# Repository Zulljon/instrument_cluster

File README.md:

View this project on [CADLAB.io](https://cadlab.io/project/2495). 

# ECU emulator v3.1a
PCB part of project (source codes unavailable!)

## Scheme

## PCB

### With FreeCAD PCB mod

### With FreeCAD KiCAD StepUp mod

## Tools
- KiCAD v4.0.7
- FreeCAD v0.15

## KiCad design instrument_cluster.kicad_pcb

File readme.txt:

Name of each file consists from name of project and it`s purpose, for example:
	Rover_Commander_v3.1a-B.Cu.gbr
		Rover_Commander_v3.1a - project name
		-B.Cu.gbr - нижний слой меди

соответственно:
	
	*-B.Cu.gbr  	-	back copper layer
	*-B.Fab.gbr 	-	footprint assemly on board`s back 
	*-B.Mask.gbr	-	solder mask on board`s back
	*-B.Paste.gbr	-	solder paste on board`s back
	*-B.SilkS.gbr	-	silkscreen on board`s back
	*-B.CrtYd.gbr	-	footprints courtyards on board`s back
	*-B.Adhes.gbr	-	adhesive on board`s back

	*-F.Cu.gbr  	-	front copper layer
	*-F.Fab.gbr 	-	footprint assemly on board`s front
	*-F.Mask.gbr	-	solder mask on board`s front
	*-F.Paste.gbr	-	solder paste on board`s front
	*-F.SilkS.gbr	-	silkscreen on board`s front
	*-F.CrtYd.gbr	-	footprints courtyards on board`s front
	*-F.Adhes.gbr	-	adhesive on board`s front

	*-Edge.Cuts.gbr	-	board`s perimeter definition
	*.drl			-	excellon drill file
	*-drl_map.gbr	-	map drill file

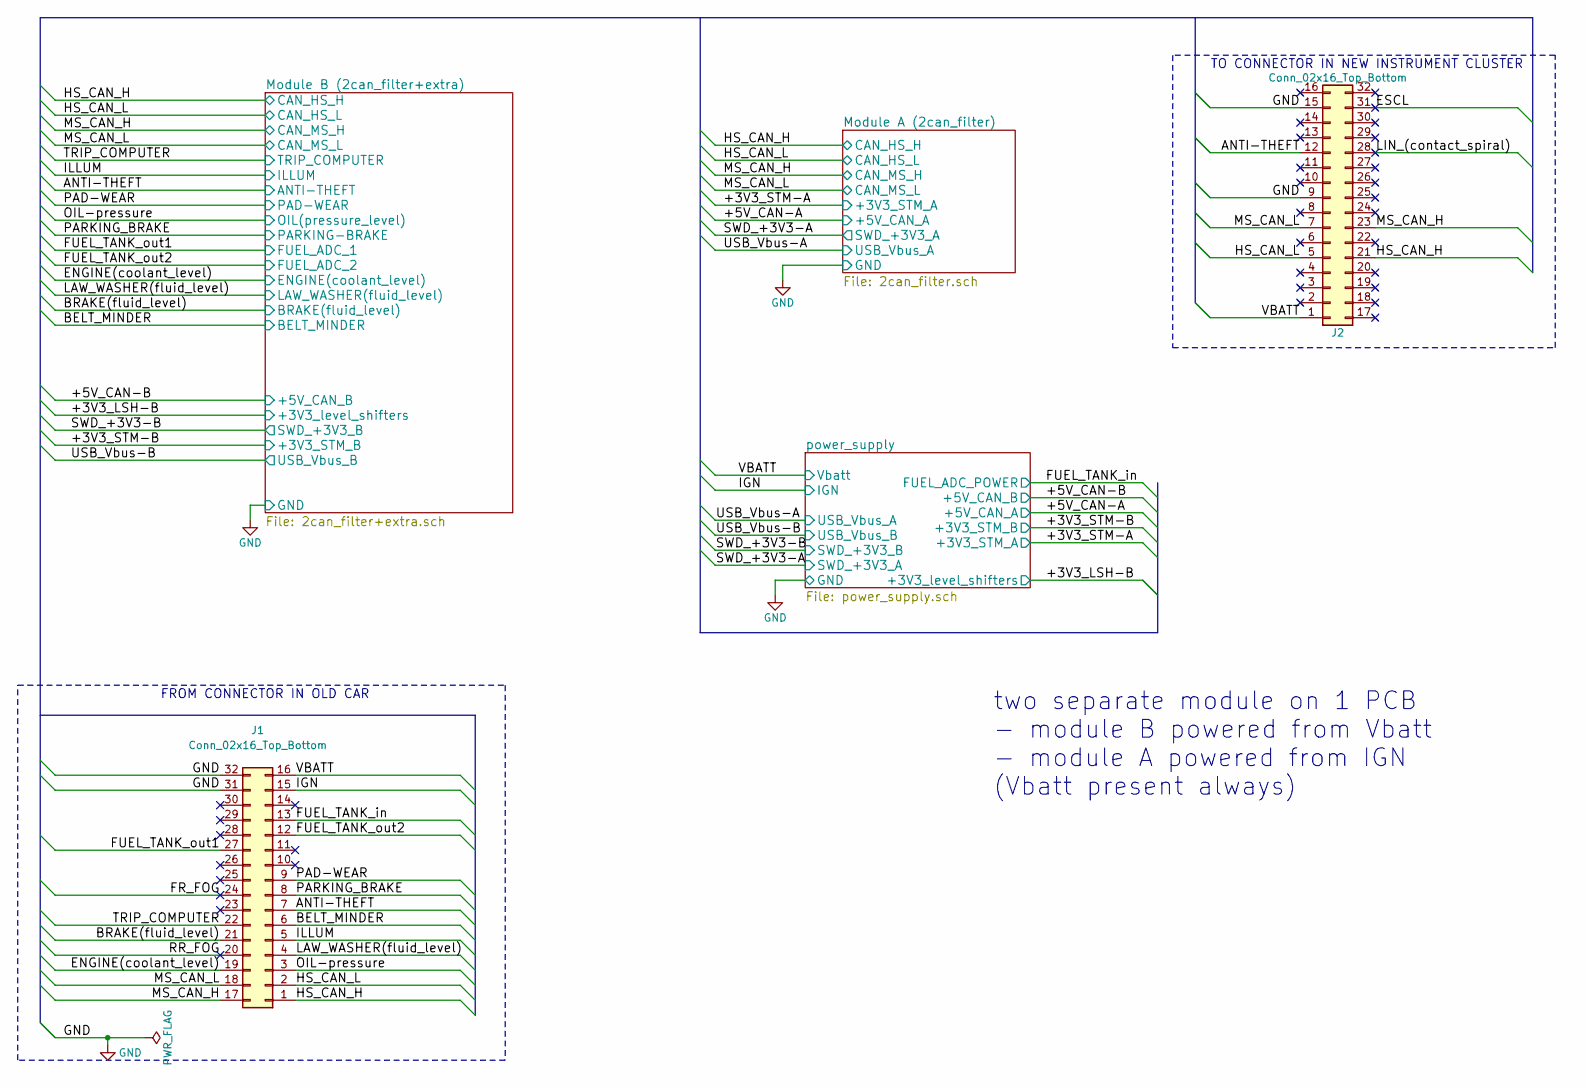
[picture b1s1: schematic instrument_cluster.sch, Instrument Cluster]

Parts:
J1: Conn_02x16_Top_Bottom; Pin_Header_Angled_2x16_Pitch2.54mm
J2: Conn_02x16_Top_Bottom; Socket_Strip_Straight_2x16_Pitch2.54mm

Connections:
/ANTI-THEFT: J1.7, J2.12; also elsewhere on the board
/BELT_MINDER: J1.6; also elsewhere on the board
/BRAKE(fluid_level): J1.21; also elsewhere on the board
/ENGINE(coolant_level): J1.19; also elsewhere on the board
/ESCL: J2.31
/FR_FOG: J1.24
/FUEL_TANK_in: J1.13; also elsewhere on the board
/FUEL_TANK_out1: J1.27; also elsewhere on the board
/FUEL_TANK_out2: J1.12; also elsewhere on the board
/HS_CAN_H: J1.1, J2.21; also elsewhere on the board
/HS_CAN_L: J1.2, J2.5; also elsewhere on the board
/IGN: J1.15; also elsewhere on the board
/ILLUM: J1.5; also elsewhere on the board
/LAW_WASHER(fluid_level): J1.4; also elsewhere on the board
/LIN_(contact_spiral): J2.28
/MS_CAN_H: J1.17, J2.23; also elsewhere on the board
/MS_CAN_L: J1.18, J2.7; also elsewhere on the board
/OIL-pressure: J1.3; also elsewhere on the board
/PAD-WEAR: J1.9; also elsewhere on the board
/PARKING_BRAKE: J1.8; also elsewhere on the board
/RR_FOG: J1.20
/TRIP_COMPUTER: J1.22; also elsewhere on the board
/VBATT: J1.16, J2.1; also elsewhere on the board
GND: J1.31, J1.32, J2.9, J2.15; also elsewhere on the board

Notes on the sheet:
FROM CONNECTOR IN OLD CAR
TO CONNECTOR IN NEW INSTRUMENT CLUSTER
two separate module on 1 PCB - module B powered from Vbatt - module A powered from IGN (Vbatt present always)

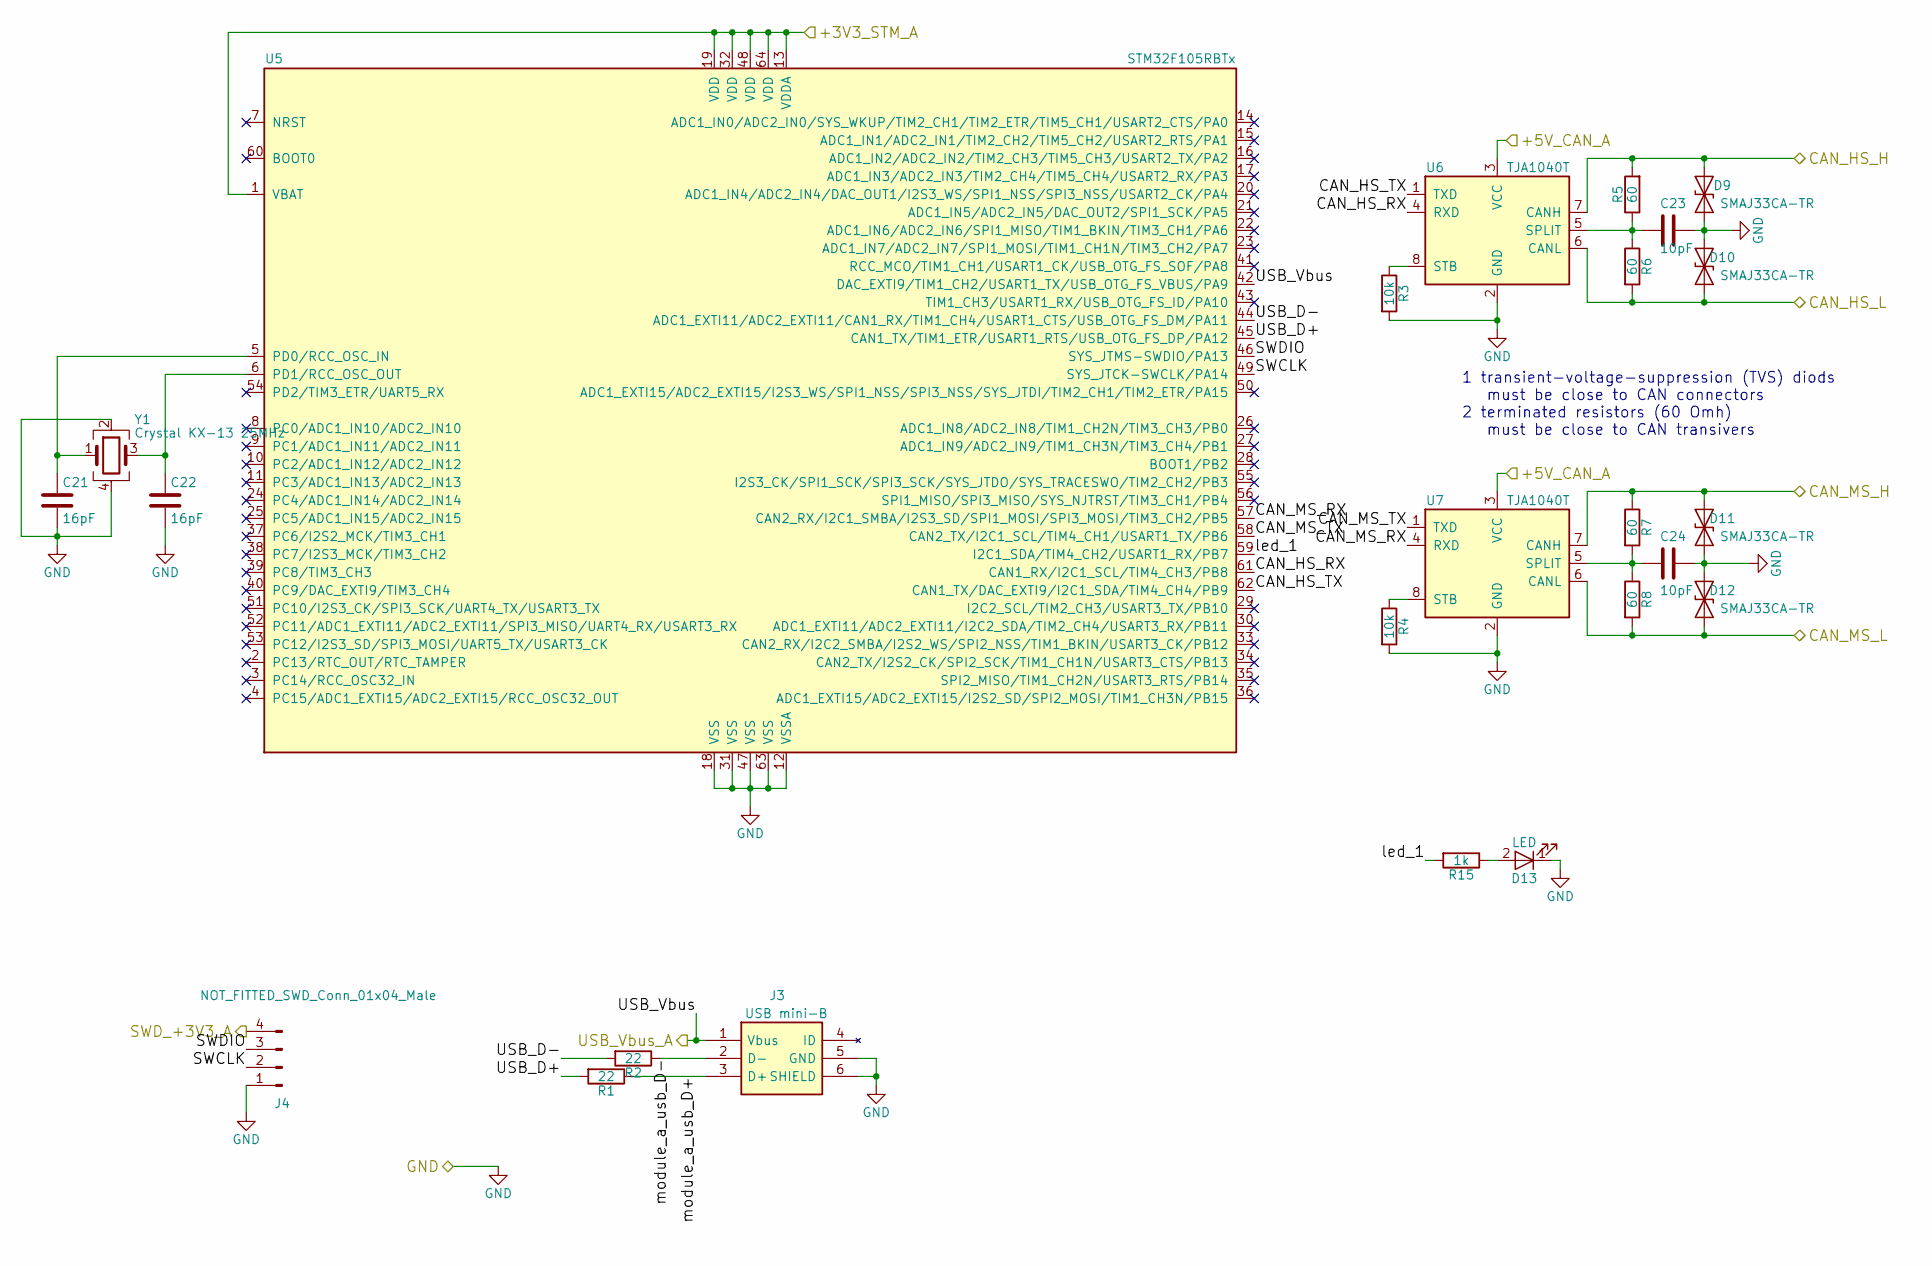
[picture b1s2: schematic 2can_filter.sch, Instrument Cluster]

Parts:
C21, C22: 16pF; C_0805
C23, C24: 10pF; C_0805
D9, D10, D11, D12: SMAJ33CA-TR; D_SMA
D13: LED; LED_0805
J3: USB mini-B; USB-B-M5-SMD-C; Manufacturer_Part_Number 54819-0572
J4: NOT_FITTED_SWD_Conn_01x04_Male; Pin_Header_Straight_1x04_Pitch2.54mm
R1, R2: 22; R_0805
R3, R4: 10k; R_0805
R5, R6, R7, R8: 60; R_0805
R15: 1k; R_0805
U5: STM32F105RBTx; LQFP-64_10x10mm_Pitch0.5mm
U6, U7: TJA1040T; SOIC-8_3.9x4.9mm_Pitch1.27mm
Y1: Crystal KX-13 25MHz; Crystal_SMD_7050-4pin_7.0x5.0mm

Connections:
/+3V3_STM-A: J4.4, U5.1 (VBAT), U5.13 (VDDA), U5.19 (VDD), U5.32 (VDD), U5.48 (VDD), U5.64 (VDD); also elsewhere on the board
/+5V_CAN-A: U6.3 (VCC), U7.3 (VCC); also elsewhere on the board
/HS_CAN_H: D9.1 (A1), R5.2, U6.7 (CANH); also elsewhere on the board
/HS_CAN_L: D10.2 (A2), R6.2, U6.6 (CANL); also elsewhere on the board
/MS_CAN_H: D11.1 (A1), R7.1, U7.7 (CANH); also elsewhere on the board
/MS_CAN_L: D12.2 (A2), R8.2, U7.6 (CANL); also elsewhere on the board
/Module A (2can_filter)/CAN_HS_RX: U5.61 (CAN1_RX/I2C1_SCL/TIM4_CH3/PB8), U6.4 (RXD)
/Module A (2can_filter)/CAN_HS_TX: U5.62 (CAN1_TX/DAC_EXTI9/I2C1_SDA/TIM4_CH4/PB9), U6.1 (TXD)
/Module A (2can_filter)/CAN_MS_RX: U5.57 (CAN2_RX/I2C1_SMBA/I2S3_SD/SPI1_MOSI/SPI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), U7.4 (RXD)
/Module A (2can_filter)/CAN_MS_TX: U5.58 (CAN2_TX/I2C1_SCL/TIM4_CH1/USART1_TX/PB6), U7.1 (TXD)
/Module A (2can_filter)/SWCLK: J4.2, U5.49 (SYS_JTCK-SWCLK/PA14)
/Module A (2can_filter)/SWDIO: J4.3, U5.46 (SYS_JTMS-SWDIO/PA13)
/Module A (2can_filter)/USB_D+: R1.2, U5.45 (CAN1_TX/TIM1_ETR/USART1_RTS/USB_OTG_FS_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)
/Module A (2can_filter)/USB_D-: R2.2, U5.44 (ADC1_EXTI11/ADC2_EXTI11/CAN1_RX/TIM1_CH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)
/Module A (2can_filter)/led_1: R15.2, U5.59 (I2C1_SDA/TIM4_CH2/USART1_RX/PB7)
/Module A (2can_filter)/module_a_usb_D+: J3.3 (D+), R1.1
/Module A (2can_filter)/module_a_usb_D-: J3.2 (D-), R2.1
/USB_Vbus-A: J3.1 (Vbus), U5.42 (DAC_EXTI9/TIM1_CH2/USART1_TX/USB_OTG_FS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); also elsewhere on the board
GND: C21.2, C22.2, C23.1, C24.1, D9.2 (A2), D10.1 (A1), D11.2 (A2), D12.1 (A1), D13.1 (K), J3.5 (GND), J3.6 (SHIELD), J4.1, R3.2, R4.2, U5.12 (VSSA), U5.18 (VSS), U5.31 (VSS), U5.47 (VSS), U5.63 (VSS), U6.2 (GND), U7.2 (GND), Y1.2, Y1.4; also elsewhere on the board
unnamed: C21.1, U5.5 (PD0/RCC_OSC_IN), Y1.1
unnamed: C22.1, U5.6 (PD1/RCC_OSC_OUT), Y1.3
unnamed: C23.2, R5.1, R6.1, U6.5 (SPLIT)
unnamed: C24.2, R7.2, R8.1, U7.5 (SPLIT)
unnamed: D13.2 (A), R15.1
unnamed: R3.1, U6.8 (STB)
unnamed: R4.1, U7.8 (STB)

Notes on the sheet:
1 transient-voltage-suppression (TVS) diods must be close to CAN connectors 2 terminated resistors (60 Omh) must be close to CAN transivers

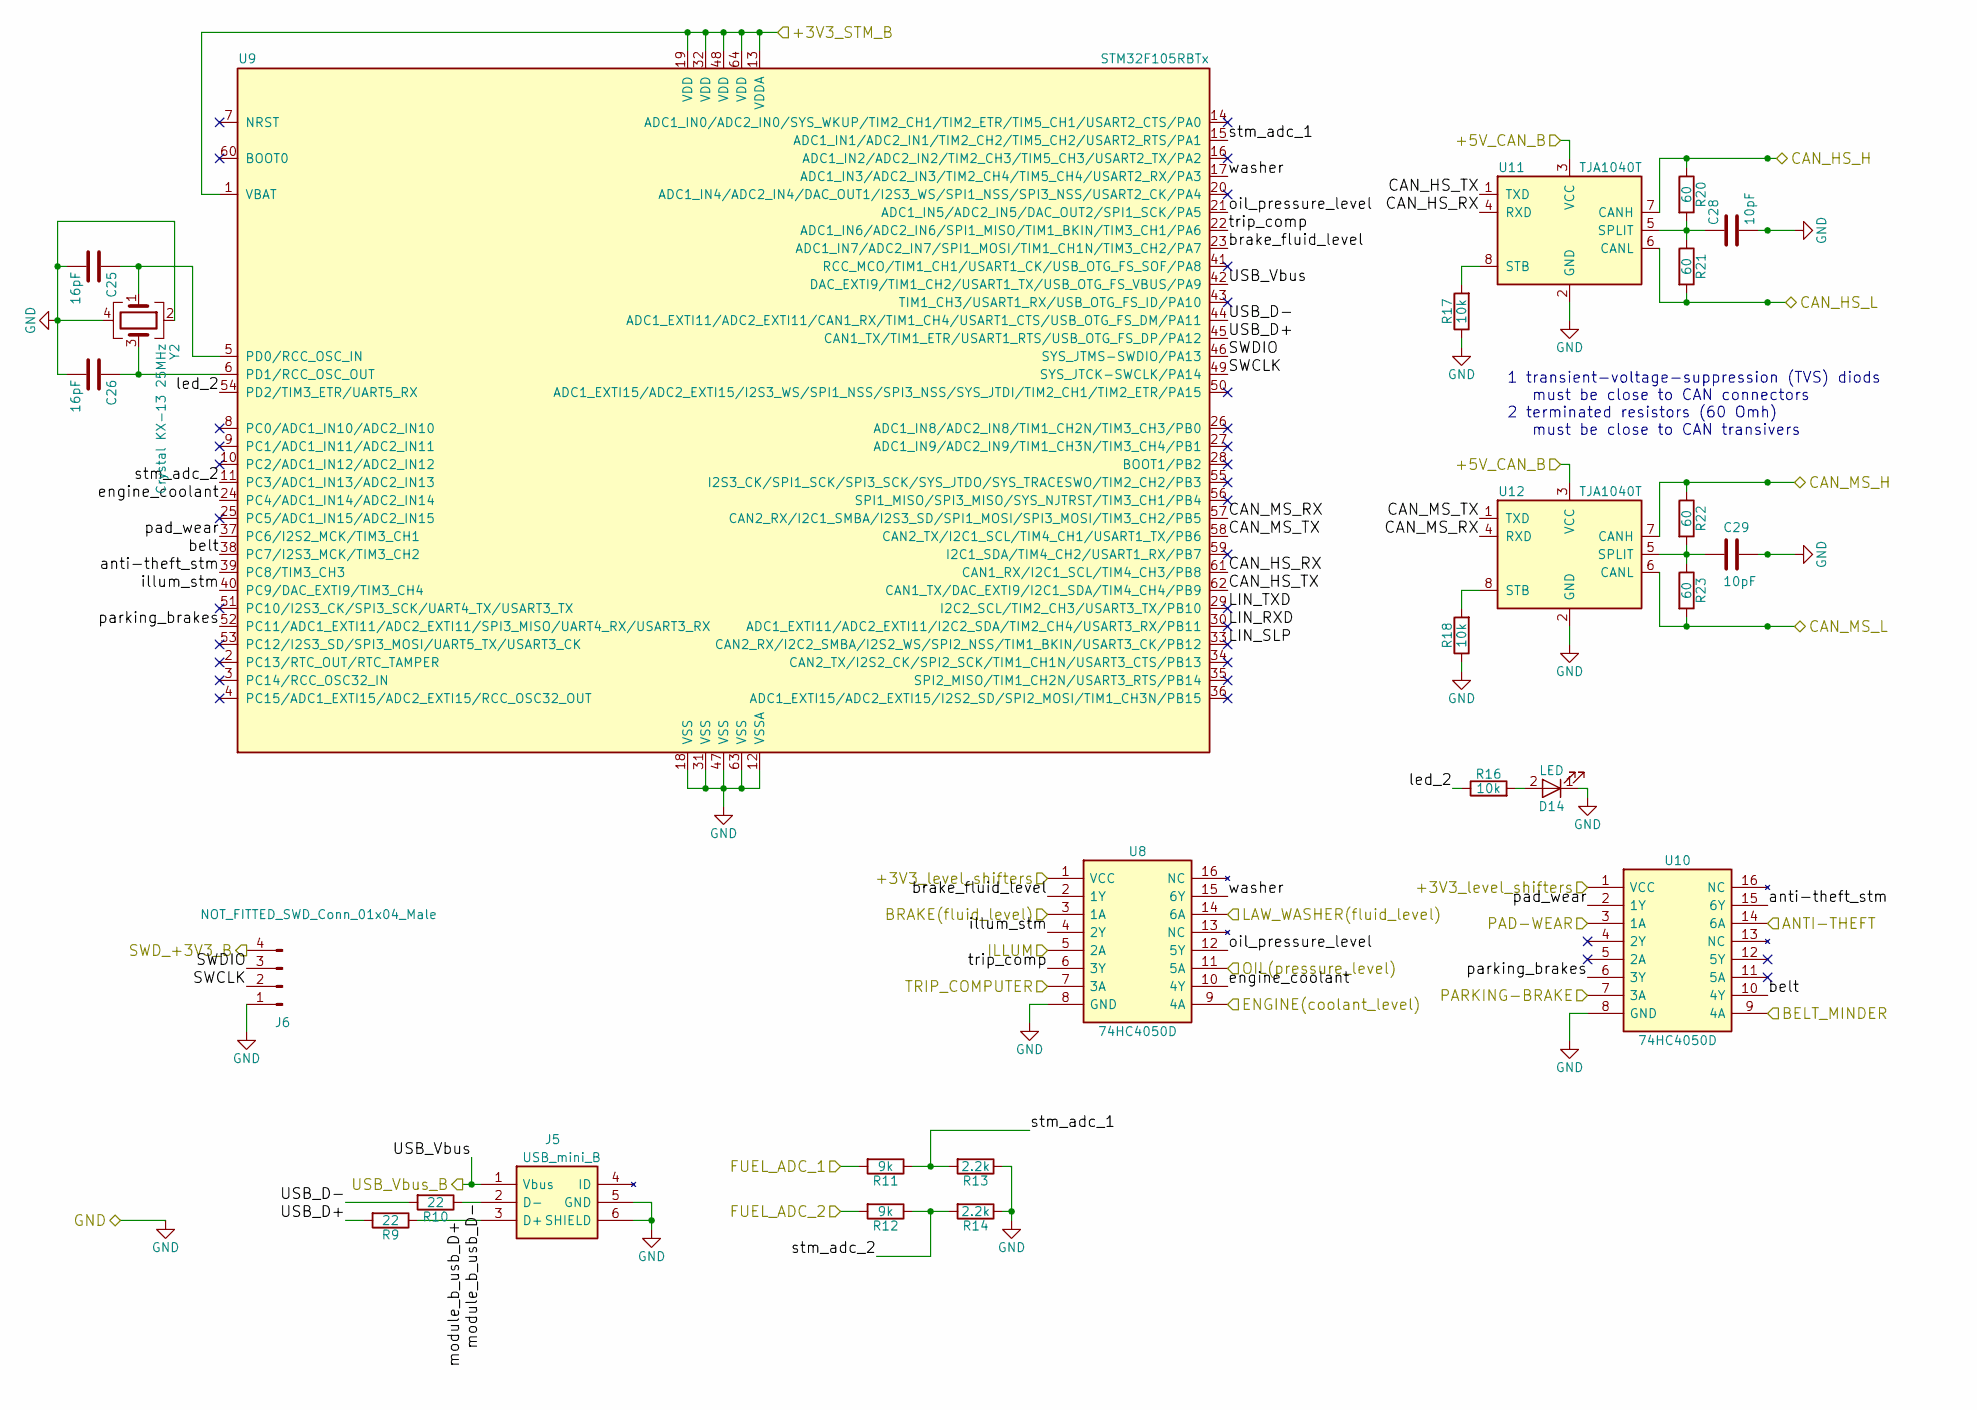
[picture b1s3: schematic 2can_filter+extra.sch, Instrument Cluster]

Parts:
C25, C26: 16pF; C_0805
C28, C29: 10pF; C_0805
D14: LED; LED_0805
J5: USB_mini_B; USB-B-M5-SMD-C; Manufacturer_Part_Number 54819-0572
J6: NOT_FITTED_SWD_Conn_01x04_Male; Pin_Header_Straight_1x04_Pitch2.54mm
R9, R10: 22; R_0805
R11, R12: 9k; R_0805
R13, R14: 2.2k; R_0805
R16, R17, R18: 10k; R_0805
R20, R21, R22, R23: 60; R_0805
U8, U10: 74HC4050D; SOIC-16_3.9x9.9mm_Pitch1.27mm; Manufacturer_Part_Number 74HC4050D
U9: STM32F105RBTx; LQFP-64_10x10mm_Pitch0.5mm
U11, U12: TJA1040T; SOIC-8_3.9x4.9mm_Pitch1.27mm
Y2: Crystal KX-13 25MHz; Crystal_SMD_7050-4pin_7.0x5.0mm

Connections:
/+3V3_LSH-B: U8.1 (VCC), U10.1 (VCC); also elsewhere on the board
/+3V3_STM-B: J6.4, U9.1 (VBAT), U9.13 (VDDA), U9.19 (VDD), U9.32 (VDD), U9.48 (VDD), U9.64 (VDD); also elsewhere on the board
/+5V_CAN-B: U11.3 (VCC), U12.3 (VCC); also elsewhere on the board
/ANTI-THEFT: U10.14 (6A); also elsewhere on the board
/BELT_MINDER: U10.9 (4A); also elsewhere on the board
/BRAKE(fluid_level): U8.3 (1A); also elsewhere on the board
/ENGINE(coolant_level): U8.9 (4A); also elsewhere on the board
/FUEL_TANK_out1: R11.2; also elsewhere on the board
/FUEL_TANK_out2: R12.2; also elsewhere on the board
/HS_CAN_H: R20.1, U11.7 (CANH); also elsewhere on the board
/HS_CAN_L: R21.2, U11.6 (CANL); also elsewhere on the board
/ILLUM: U8.5 (2A); also elsewhere on the board
/LAW_WASHER(fluid_level): U8.14 (6A); also elsewhere on the board
/MS_CAN_H: R22.1, U12.7 (CANH); also elsewhere on the board
/MS_CAN_L: R23.2, U12.6 (CANL); also elsewhere on the board
/Module B (2can_filter+extra)/CAN_HS_RX: U9.61 (CAN1_RX/I2C1_SCL/TIM4_CH3/PB8), U11.4 (RXD)
/Module B (2can_filter+extra)/CAN_HS_TX: U9.62 (CAN1_TX/DAC_EXTI9/I2C1_SDA/TIM4_CH4/PB9), U11.1 (TXD)
/Module B (2can_filter+extra)/CAN_MS_RX: U9.57 (CAN2_RX/I2C1_SMBA/I2S3_SD/SPI1_MOSI/SPI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), U12.4 (RXD)
/Module B (2can_filter+extra)/CAN_MS_TX: U9.58 (CAN2_TX/I2C1_SCL/TIM4_CH1/USART1_TX/PB6), U12.1 (TXD)
/Module B (2can_filter+extra)/LIN_RXD: U9.30 (ADC1_EXTI11/ADC2_EXTI11/I2C2_SDA/TIM2_C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)
/Module B (2can_filter+extra)/LIN_SLP: U9.33 (CAN2_RX/I2C2_SMBA/I2S2_WS/SPI2_NSS/TIM1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)
/Module B (2can_filter+extra)/LIN_TXD: U9.29 (I2C2_SCL/TIM2_CH3/USART3_TX/PB10)
/Module B (2can_filter+extra)/SWCLK: J6.2, U9.49 (SYS_JTCK-SWCLK/PA14)
/Module B (2can_filter+extra)/SWDIO: J6.3, U9.46 (SYS_JTMS-SWDIO/PA13)
/Module B (2can_filter+extra)/USB_D+: R9.2, U9.45 (CAN1_TX/TIM1_ETR/USART1_RTS/USB_OTG_FS_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)
/Module B (2can_filter+extra)/USB_D-: R10.2, U9.44 (ADC1_EXTI11/ADC2_EXTI11/CAN1_RX/TIM1_CH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)
/Module B (2can_filter+extra)/anti-theft_stm: U9.39 (PC8/TIM3_CH3), U10.15 (6Y)
/Module B (2can_filter+extra)/belt: U9.38 (PC7/I2S3_MCK/TIM3_CH2), U10.10 (4Y)
/Module B (2can_filter+extra)/brake_fluid_level: U8.2 (1Y), U9.23 (ADC1_IN7/ADC2_IN7/SPI1_MOSI/TIM1_CH1N/T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)
/Module B (2can_filter+extra)/engine_coolant: U8.10 (4Y), U9.24 (PC4/ADC1_IN14/ADC2_IN14)
/Module B (2can_filter+extra)/illum_stm: U8.4 (2Y), U9.40 (PC9/DAC_EXTI9/TIM3_CH4)
/Module B (2can_filter+extra)/led_2: R16.1, U9.54 (PD2/TIM3_ETR/UART5_RX)
/Module B (2can_filter+extra)/module_b_usb_D+: J5.3 (D+), R9.1
/Module B (2can_filter+extra)/module_b_usb_D-: J5.2 (D-), R10.1
/Module B (2can_filter+extra)/oil_pressure_level: U8.12 (5Y), U9.21 (ADC1_IN5/ADC2_IN5/DAC_OUT2/SPI1_SCK/PA5)
/Module B (2can_filter+extra)/pad_wear: U9.37 (PC6/I2S2_MCK/TIM3_CH1), U10.2 (1Y)
/Module B (2can_filter+extra)/parking_brakes: U9.52 (PC11/ADC1_EXTI11/ADC2_EXTI11/SPI3_MISO/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), U10.6 (3Y)
/Module B (2can_filter+extra)/stm_adc_1: R11.1, R13.2, U9.15 (ADC1_IN1/ADC2_IN1/TIM2_CH2/TIM5_CH2/USA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)
/Module B (2can_filter+extra)/stm_adc_2: R12.1, R14.2, U9.11 (PC3/ADC1_IN13/ADC2_IN13)
/Module B (2can_filter+extra)/trip_comp: U8.6 (3Y), U9.22 (ADC1_IN6/ADC2_IN6/SPI1_MISO/TIM1_BKIN/T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)
/Module B (2can_filter+extra)/washer: U8.15 (6Y), U9.17 (ADC1_IN3/ADC2_IN3/TIM2_CH4/TIM5_CH4/USA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)
/OIL-pressure: U8.11 (5A); also elsewhere on the board
/PAD-WEAR: U10.3 (1A); also elsewhere on the board
/PARKING_BRAKE: U10.7 (3A); also elsewhere on the board
/TRIP_COMPUTER: U8.7 (3A); also elsewhere on the board
/USB_Vbus-B: J5.1 (Vbus), U9.42 (DAC_EXTI9/TIM1_CH2/USART1_TX/USB_OTG_FS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); also elsewhere on the board
GND: C25.2, C26.2, C28.2, C29.1, D14.1 (K), J5.5 (GND), J5.6 (SHIELD), J6.1, R13.1, R14.1, R17.1, R18.1, U8.8 (GND), U9.12 (VSSA), U9.18 (VSS), U9.31 (VSS), U9.47 (VSS), U9.63 (VSS), U10.8 (GND), U11.2 (GND), U12.2 (GND), Y2.2, Y2.4; also elsewhere on the board
unnamed: C25.1, U9.5 (PD0/RCC_OSC_IN), Y2.1
unnamed: C26.1, U9.6 (PD1/RCC_OSC_OUT), Y2.3
unnamed: C28.1, R20.2, R21.1, U11.5 (SPLIT)
unnamed: C29.2, R22.2, R23.1, U12.5 (SPLIT)
unnamed: D14.2 (A), R16.2
unnamed: R17.2, U11.8 (STB)
unnamed: R18.2, U12.8 (STB)

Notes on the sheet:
1 transient-voltage-suppression (TVS) diods must be close to CAN connectors 2 terminated resistors (60 Omh) must be close to CAN transivers

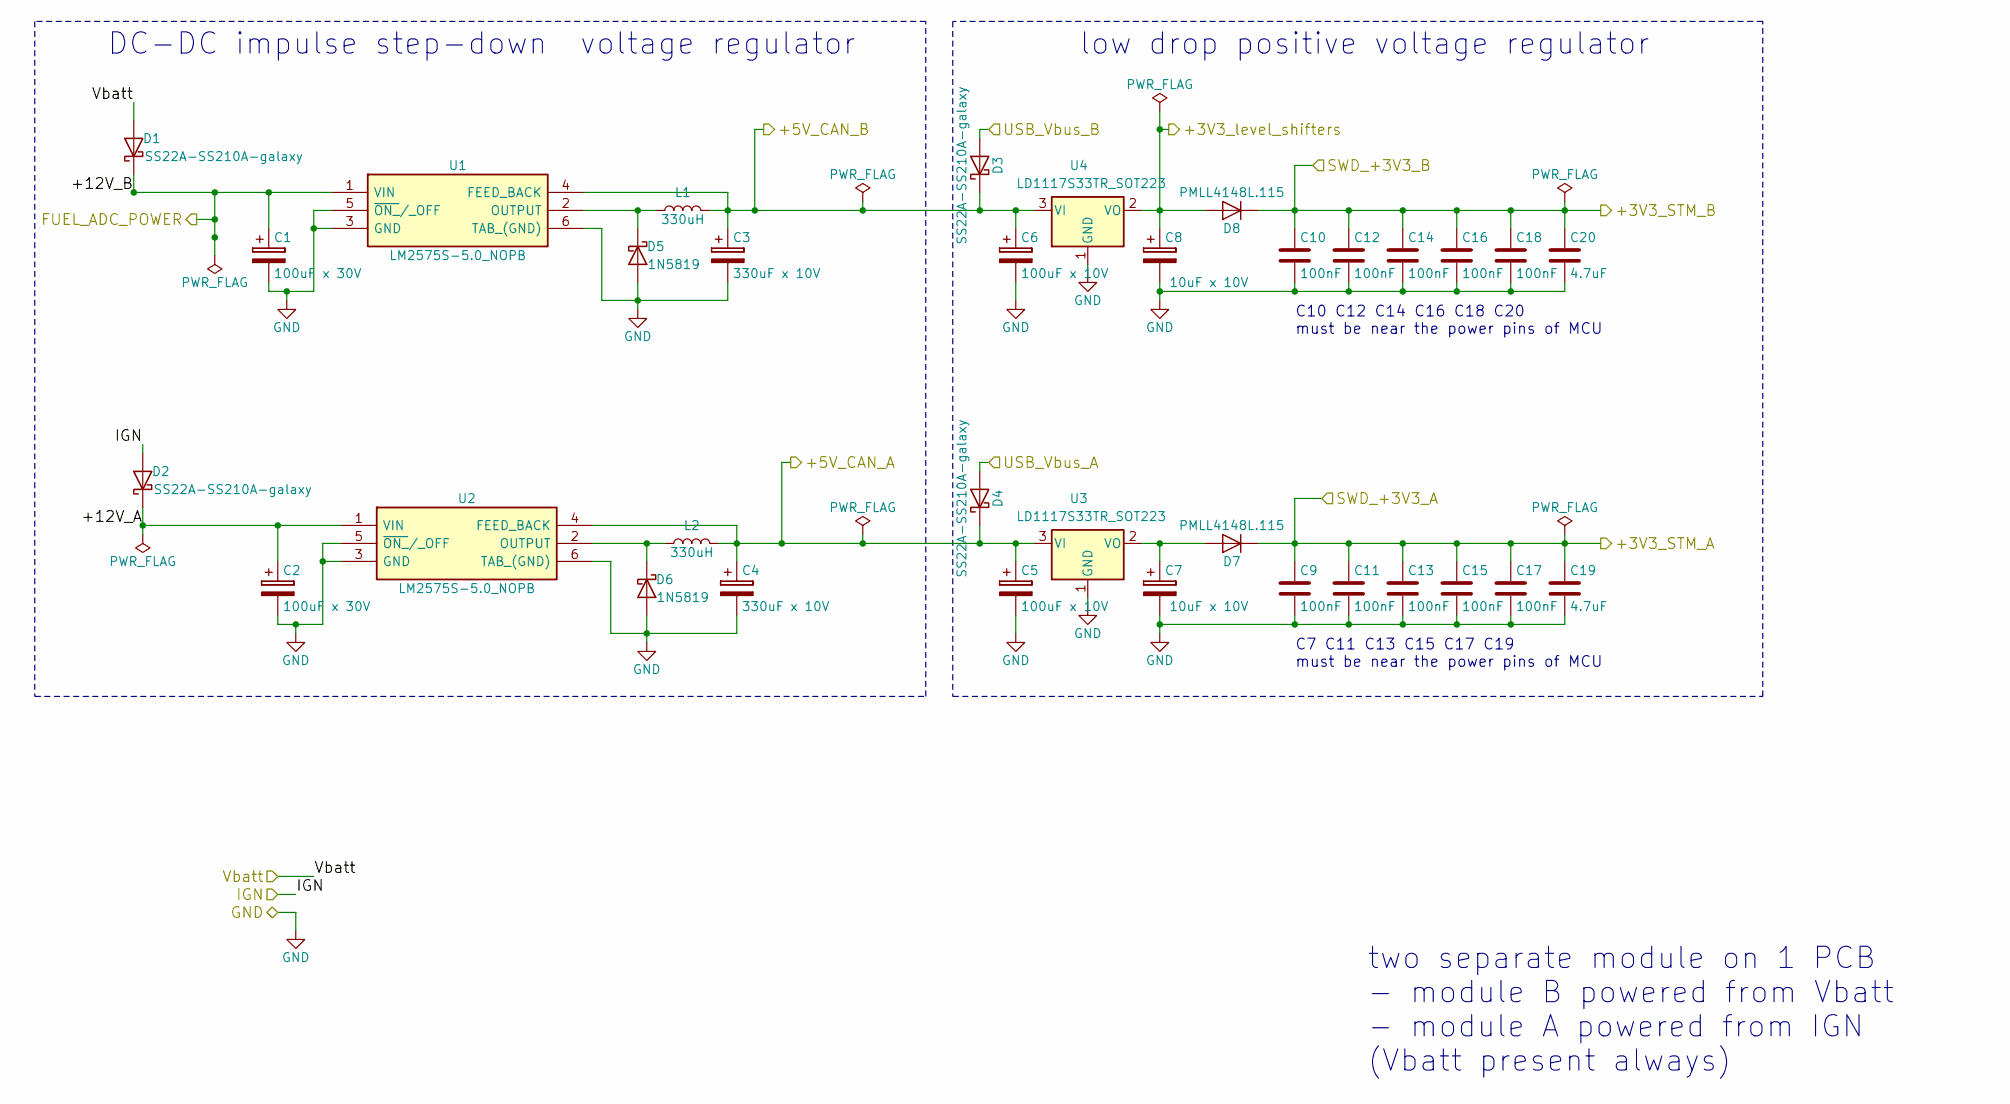
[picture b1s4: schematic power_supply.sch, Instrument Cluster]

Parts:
C1, C2: 100uF x 30V; CP_Elec_6.3x7.7
C3, C4: 330uF x 10V; CP_Elec_8x10
C5, C6: 100uF x 10V; CP_Tantalum_Case-D_EIA-7343-31_Hand
C7, C8: 10uF x 10V; CP_Tantalum_Case-B_EIA-3528-21_Wave
C9, C10, C11, C12, C13, C14, C15, C16, C17, C18: 100nF; C_0805
C19, C20: 4.7uF; C_0805
D1, D2, D3, D4: SS22A-SS210A-galaxy; D_SMA
D5, D6: 1N5819; D_SOD-123
D7, D8: PMLL4148L.115; D_SC-80
L1, L2: 330uH; L_12x12mm_h8mm
U1, U2: LM2575S-5.0_NOPB; TO-263-5_TabPin6; Manufacturer_Part_Number LM2575S-5.0/NOPB
U3, U4: LD1117S33TR_SOT223; SOT-223-3_TabPin2

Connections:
/+3V3_LSH-B: C8.1, D8.2 (A), U4.2 (VO); also elsewhere on the board
/+3V3_STM-A: C9.1, C11.1, C13.1, C15.1, C17.1, C19.1, D7.1 (K); also elsewhere on the board
/+3V3_STM-B: C10.1, C12.1, C14.1, C16.1, C18.1, C20.1, D8.1 (K); also elsewhere on the board
/+5V_CAN-A: C4.1, C5.1, D4.1 (K), L2.2, U2.4 (FEED_BACK), U3.3 (VI); also elsewhere on the board
/+5V_CAN-B: C3.1, C6.1, D3.1 (K), L1.2, U1.4 (FEED_BACK), U4.3 (VI); also elsewhere on the board
/FUEL_TANK_in: C1.1, D1.1 (K), U1.1 (VIN); also elsewhere on the board
/IGN: D2.2 (A); also elsewhere on the board
/USB_Vbus-A: D4.2 (A); also elsewhere on the board
/USB_Vbus-B: D3.2 (A); also elsewhere on the board
/VBATT: D1.2 (A); also elsewhere on the board
/power_supply/+12V_A: C2.1, D2.1 (K), U2.1 (VIN)
GND: C1.2, C2.2, C3.2, C4.2, C5.2, C6.2, C7.2, C8.2, C9.2, C10.2, C11.2, C12.2, C13.2, C14.2, C15.2, C16.2, C17.2, C18.2, C19.2, C20.2, D5.2 (A), D6.2 (A), U1.3 (GND), U1.5 (~ON_~/_OFF), U1.6 (TAB_(GND)), U2.3 (GND), U2.5 (~ON_~/_OFF), U2.6 (TAB_(GND)), U3.1 (GND), U4.1 (GND); also elsewhere on the board
unnamed: C7.1, D7.2 (A), U3.2 (VO)
unnamed: D5.1 (K), L1.1, U1.2 (OUTPUT)
unnamed: D6.1 (K), L2.1, U2.2 (OUTPUT)

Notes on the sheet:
DC-DC impulse step-down voltage regulator
low drop positive voltage regulator
two separate module on 1 PCB - module B powered from Vbatt - module A powered from IGN (Vbatt present always)
C7 C11 C13 C15 C17 C19 must be near the power pins of MCU
C10 C12 C14 C16 C18 C20 must be near the power pins of MCU

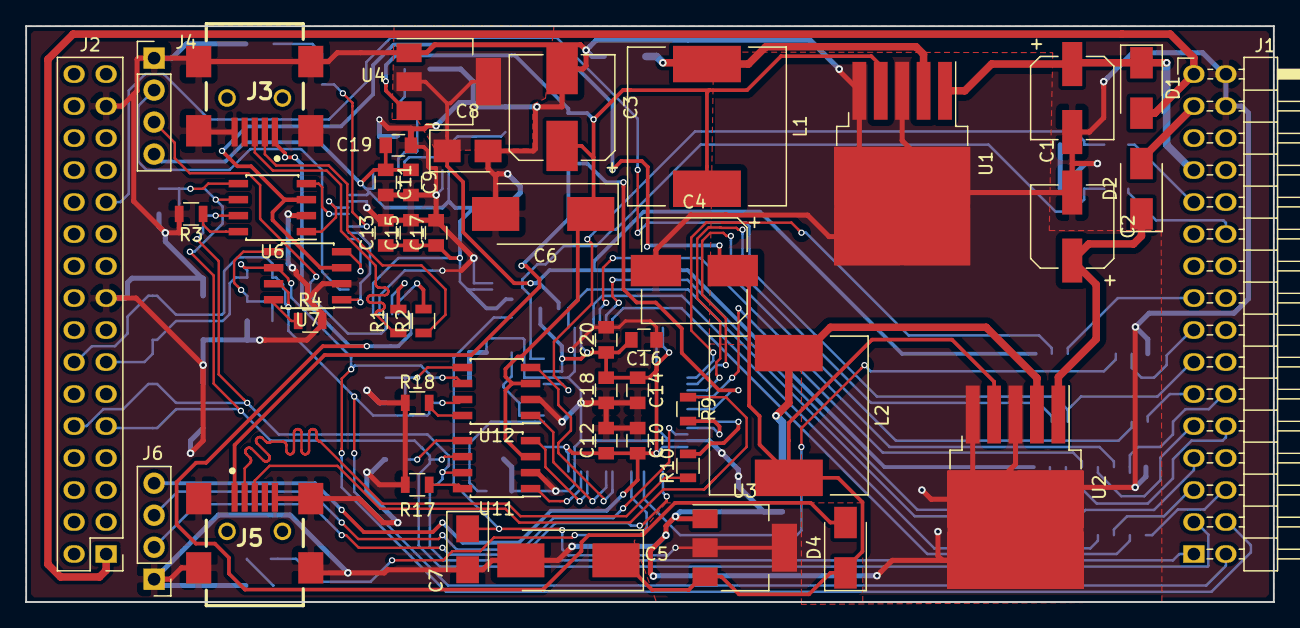
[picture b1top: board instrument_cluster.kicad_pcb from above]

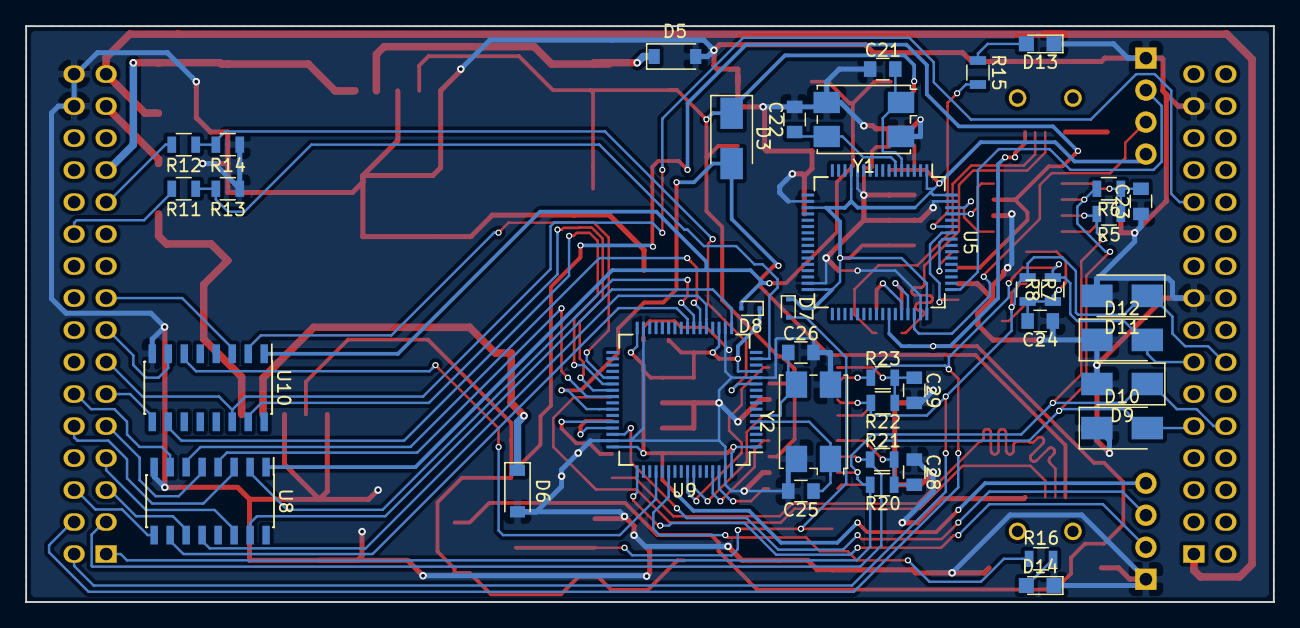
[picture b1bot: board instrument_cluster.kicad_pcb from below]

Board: 2 copper layers, 99.1 x 45.7 mm, 86 parts (39 on the bottom side), 79 nets.

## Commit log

2017-11-11 remove BOM from gitignore
2017-11-11 add git readme
2017-11-11 add graphics for readme
2017-11-15 finish scheme & change libs path
2017-11-15 specify footpints to resistors and capasitors
2017-11-15 switch to my labrary https://github.com/Zulljon/zpkl
2017-11-16 add missed footprints, add additional capasitors on 3.3V line, fix banch of ERC errors
2017-11-16 add footprints to SWD connectors
2017-11-16 change usb fp
2017-11-16 create PCB and import fp from netlist
2017-11-16 rescue the stm32 mcu_s, add pcb list info
2017-11-16 fix D3 D4 diods connections
2017-11-16 pcb part replace
2017-11-17 fix margins, circuit to edge more >=0.3 mm
2017-11-17 setup design rule
2017-11-17 setup design rule2
2017-11-17 power converters placement complete
2017-11-17 fix labels in fuel_adc
2017-11-17 change connectivity of level-shifters(on sheme and pcb)
2017-11-17 fill both side with GND, add heat exchange with lm2575
2017-11-18 add commentary to scheme
2017-11-18 working with pcb design
2017-11-18 redone shematic of power supply, fix usb_vbus and swd diods connections, change mcu capacitors connections
2017-11-20 reduce board edge, finish module B tracing
2017-11-22 switch to relative libs path
2017-11-22 add transient voltage suppression diods on CAN
2017-11-22 work on module A
2017-11-23 add resistor on can STB pin module A
2017-11-23 TODO swd module A, anti-theft
2017-11-24 pcb tracing finish
2017-11-24 update graphics for readme file
2017-11-25 fix signal trace length usb module A
2017-12-02 fix files mods(permission)
2017-12-05 sch&pcb: add LED`s and refresh readme image`s
2017-12-05 add usb 3d modele
2017-12-06 add shell script to zip gerbers
2017-12-06 add gerbers files
2017-12-06 zipped gerber files
2017-12-08 add descriptions for gerber files
2017-12-08 add BOM file
2018-02-05 fix libs paths
2018-04-16 fix USB, swapped the traces D+ D-
2018-04-16 fix CAN, swapped the stm->to->can connection in module B
2018-04-17 fix USB footprint
2020-02-15 Backlink to CADLAB.io has been added.
